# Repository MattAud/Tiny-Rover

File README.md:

# Tiny-Rover
A modification of Adafruit's  Trinket Powered Rover to function as a tabletop scale RC tank

The Adafruit Trinket Rover ( https://learn.adafruit.com/trinket-powered-rover/red-rover ) is a cool starter project. The only drawback is that the treads are those woven wrist bands and I can't find them cheaply. I've created a replacement drive wheel and idler that mimic the same design, but instead take standard silicone wrist bands that are readily available on online retailers like Amazon.

These wrist bands are typically available in two sizes- youth (7 in) and adult (8 in). I have only tried this with the YOUTH size. If you try this with the adult size, your mileage may vary.

# Tiny-Tank

The other part of this is that I want to make a small, cheap RC tank. 

It will be powered by an Arduino Mini Pro (since I have ~10 laying around). I'm using the 5v variant. It will have a laser cannon that will fire and light sensors that will detect hits from enemy tanks. It will also have a buzzer for sound effects and indicator LEDs to show have many lives the tank still has.

The TX/RX is the super cheap, 4 channel RF modules available on eBay/Amazon for dirt cheap. I shose them for their cheapness and the ability to set the channels on them.

The light sensors are your typical photoresistors that are "extended" through straws. When the straws have a laser shone on them at 3", there is still a noticible jump in the code's analog reading.

The first iteration was tested and works! The only problems still are mechanical with the chassis throwing track.

The second iteration of the board was designed and ordered.

# Problems to still troubleshoot:

- The continuous diameter of the drive wheel and idler cause the tank to throw track. Aaron suggested adding a bevel on the inside.

- Board schematic MkII is in! It includes an on/off switch, is smaller in size, and has solder points for AA/AAA battery packs OR a 2cell, 7.4v lipo battery.

- The trimpot can be used to adjust the sensitivity of the light sensor threshold. An alternative could be that during the setup loop a number of measurements are taken and averaged.

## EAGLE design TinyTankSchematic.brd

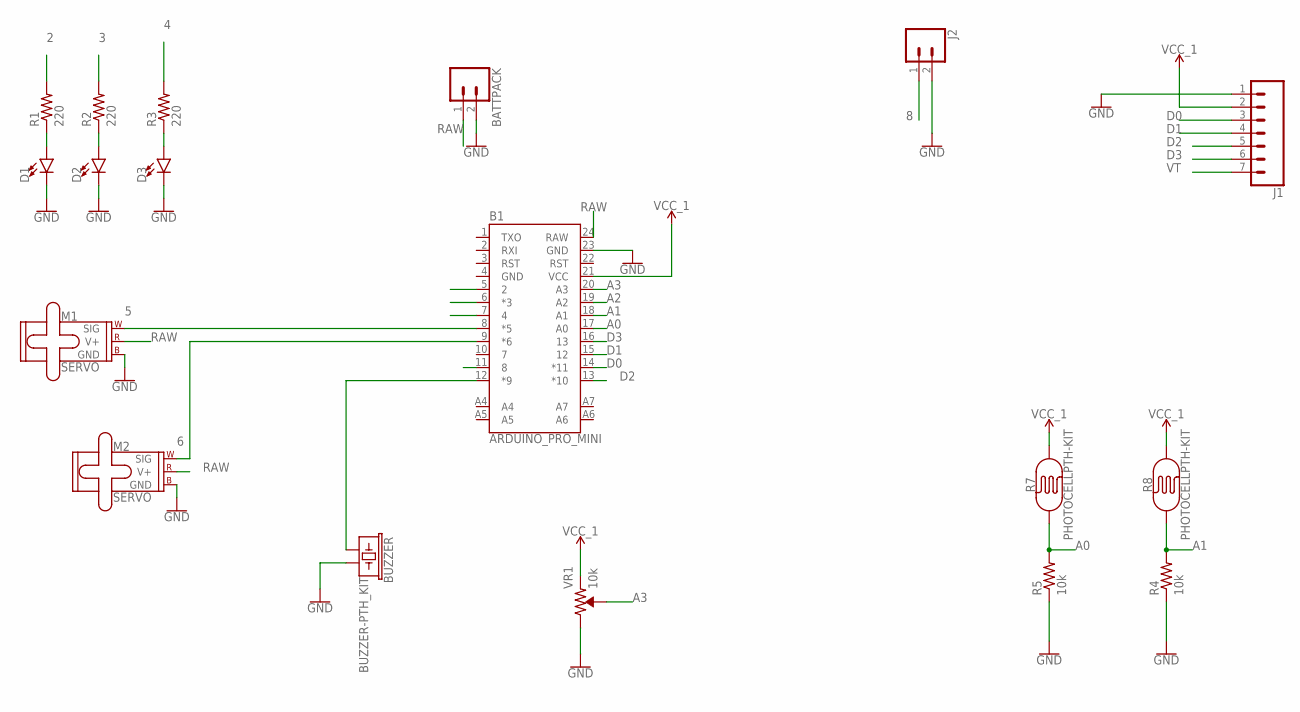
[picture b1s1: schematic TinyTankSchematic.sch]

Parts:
B1: ARDUINO_PRO_MINI
BATTPACK: CONN_02POLAR; MOLEX-1X2
BUZZER: BUZZER-PTH_KIT; BUZZER-12MM-KIT
D1, D2, D3: LED5MM; LED_5MM
J1: CONN_07; 1X07
J2: CONN_02PTH3; 1X02_LONGPADS
M1, M2: SERVO; 1X03
R1, R2, R3: 220; 0204/7
R4, R5: 10k; 0204/7
R7, R8: PHOTOCELLPTH-KIT; PHOTOCELL-KIT
VR1: 10k; TRIMPOT-PTH-3386U

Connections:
2: B1.5 (2), R1.2
3: B1.6 (*3), R2.2
4: B1.7 (4), R3.2
5: B1.8 (*5), M1.1 (SIG)
6: B1.9 (*6), M2.1 (SIG)
8: B1.11 (8), J2.1
A0: B1.17 (A0), R5.2, R7.1
A1: B1.18 (A1), R4.2, R8.1
A2: B1.19 (A2)
A3: B1.20 (A3), VR1.2 (WIPER)
D0: B1.14 (*11), J1.3
D1: B1.15 (12), J1.4
D2: B1.13 (*10), J1.5
D3: B1.16 (13), J1.6
GND: B1.4 (GND), B1.23 (GND), BATTPACK.2, BUZZER.- (2), D1.K (C), D2.K (C), D3.K (C), J1.1, J2.2, M1.3 (GND), M2.3 (GND), R4.1, R5.1, VR1.3 (CW)
unnamed: D1.A, R1.1
unnamed: D2.A, R2.1
unnamed: D3.A, R3.1
unnamed: B1.12 (*9), BUZZER.+ (1)
RAW: B1.24 (RAW), BATTPACK.1, M1.2 (V+), M2.2 (V+)
VCC_1: B1.21 (VCC), J1.2, R7.2, R8.2, VR1.1 (CCW)
VT: J1.7

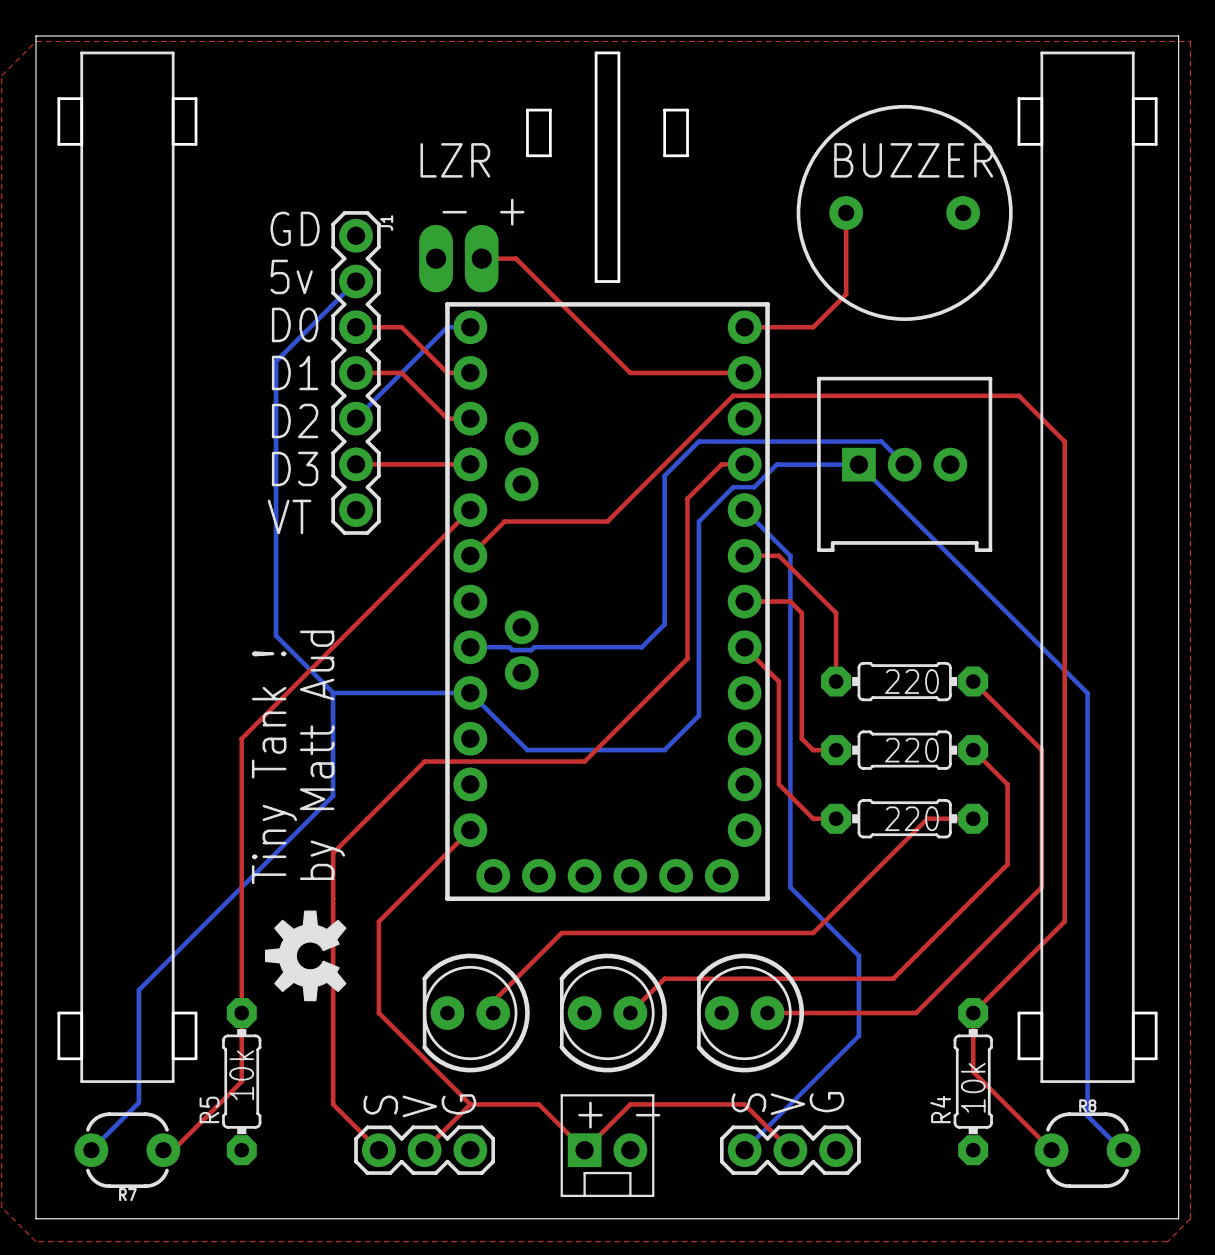
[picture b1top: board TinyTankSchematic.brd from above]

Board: 2 copper layers, 63.3 x 65.6 mm, 19 parts (0 on the bottom side), 20 nets.

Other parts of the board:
U$1: OSHW-LOGO-M

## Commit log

2018-06-14 Update README.md
    Added details to the read me
2018-06-14 3d Files for Modified Wheels
2018-06-18 Added details about the Tiny-Tank
2018-06-18 Added Arduino Sketch, Eagle Files
2018-07-11 Added RFTankFull.ino
    RFTankFull is the latest Arduino sketch. It is still not at full capacity. See the internal notes for the rundown of what still needs to change.
2018-07-24 Full capability Tank arduino sketch

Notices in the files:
parts and their libraries:
SparkFun-Boards: Licensing: Creative Commons ShareAlike 4.0 International - https://creativecommons.org/licenses/by-sa/4.0
